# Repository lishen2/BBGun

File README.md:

BBGun
=============
BBGUN is an infrared shooting system used for entertainment purposes. The project Milestag gave us a lot of inspiration.

Hareware resources
-------
* one TSAL6100 IR emitter, two HS0038B IR reciver.
* one RJ9 socket used to connect external reciver(not implemented yet).
* one three key dil switch, used to set group.
* one buzzer controlled by PWM pin.
* two push buttons.

Progress
--------
20150427: First PCB design.     
20150503: Make first test board.  
20150505: LED driver code and buzzer driver code finish.  
20150510: Finish all drivers except IR system.

Developing blog
--------
http://lsgeek.blogspot.com

BBGun
=============
BBGun是一个用于娱乐目的的红外射击系统(真人CS)。Milestag项目给了我们很多启发。

硬件资源
-------
* 一个TSAL6100发射管，两个HS0038B接收管
* 一个RJ9接口用于连接外置接收器（暂未实现）
* 一个三键拨码开关，用于设置分组
* 一个PWM引脚控制的蜂鸣器
* 两个按键

当前进度
--------
20150427: 完成PCB设计   
20150503: 完成第一块PCB的制作   
20150505: 完成LED驱动、蜂鸣器驱动  
20150510: 完成除IR系统外的所有驱动

开发博客
--------
http://blog.sina.com.cn/lgeek

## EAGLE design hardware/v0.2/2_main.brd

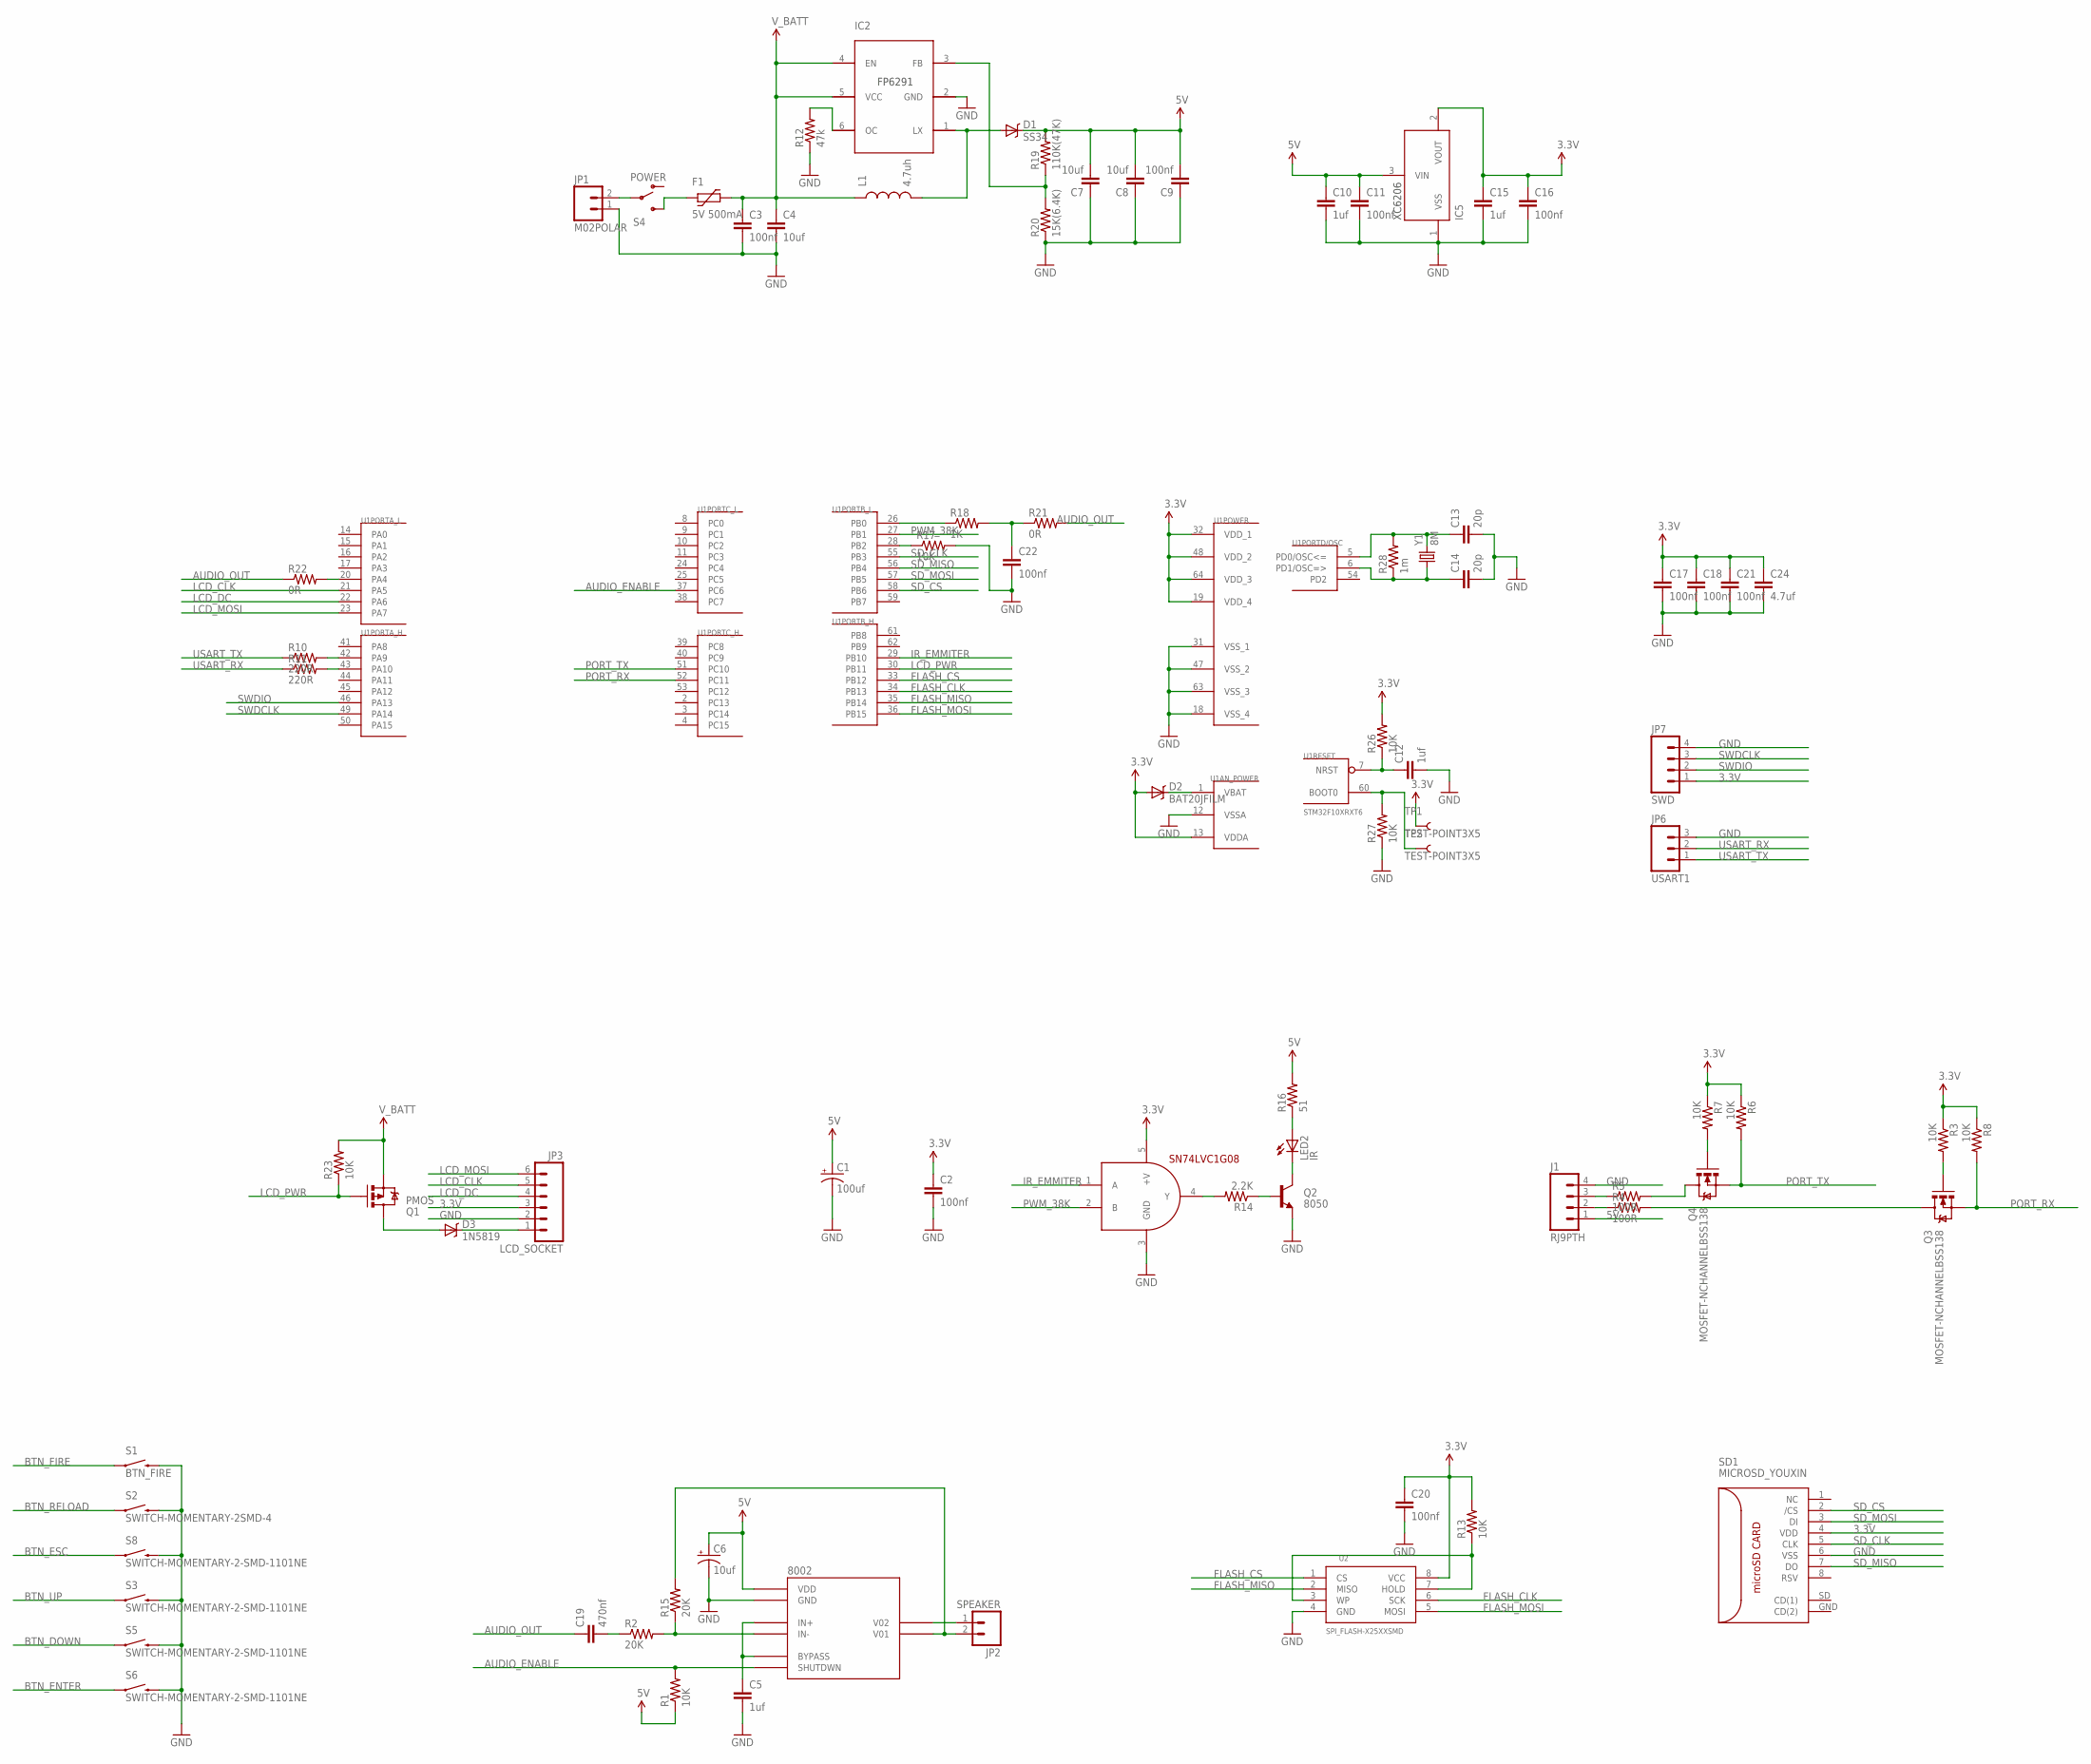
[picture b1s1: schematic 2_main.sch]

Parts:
8002: LM4871; SO08
C1: 100uf; EIA6032
C2, C3, C9, C11, C16, C17, C18, C20, C21, C22: 100nf; 0603-CAP
C4, C7, C8: 10uf; 0603-CAP
C5, C10, C12, C15: 1uf; 0603-CAP
C6: 10uf; EIA3216-KIT
C13, C14: 20p; 0603-CAP
C19: 470nf; 0603-CAP
C24: 4.7uf; 0603-CAP
D1: SS34; SMA-DIODE
D2: BAT20JFILM; SOD-323
D3: 1N5819; SOD-323
F1: 5V 500mA; R0805
IC1: SN74LVC1G08; SOT23-5
IC2: FP6291; SOT23-6
IC5: XC6206; SOT23-3
J1: RJ9PTH; RJ9
JP1: M02POLAR; MOLEX-1X2
JP2: SPEAKER; MOLEX-1X2
JP3: LCD_SOCKET; MOLEX-1X6
JP6: USART1; 1X03
JP7: SWD; 1X04
L1: 4.7uh; CR75_V2
LED2: IR; LED5MM
Q1: PMOS; SOT23-3
Q2: 8050; SOT23
Q3, Q4: MOSFET-NCHANNELBSS138; SOT23
R1, R3, R6, R7, R8, R13, R17, R23, R26, R27: 10K; 0603-RES
R2, R15: 20K; 0603-RES
R4, R5: 100R; 0603-RES
R10, R11: 220R; 0603-RES
R12: 47k; 0603-RES
R14: 2.2K; 0603-RES
R16: 51; 0603-RES
R18: 1K; 0603-RES
R19: 110K(47K); 0603-RES
R20: 15K(6.4K); 0603-RES
R21, R22: 0R; 0603-RES
R28: 1m; 0603-RES
S1: BTN_FIRE; TACTILE_SWITCH_TALL
S2: SWITCH-MOMENTARY-2SMD-4; TACTILE_SWITCH_TALL
S3, S5, S6, S8: SWITCH-MOMENTARY-2-SMD-1101NE; TACTILE-SWITCH-1101NE
S4: POWER; SWITCH-SPDT-AM#6
SD1: MICROSD_YOUXIN; MICRO_SD_YOUXIN
TP1, TP2: TEST-POINT3X5; PAD.03X.05
U1: STM32F10XRXT6; TQFP64
U2: SPI_FLASH-X25XXSMD; SO08
Y1: 8M; CRYSTAL-TXC-7A

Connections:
3.3V: C2.1, C15.1, C16.1, C17.1, C18.1, C20.1, C21.1, C24.1, D2.2 (A), IC1.5 (+V), IC5.2 (VOUT), JP3.3, JP7.1, R3.1, R6.1, R7.1, R8.1, R13.2, R26.2, SD1.4 (VDD), TP1.P$1, U1.13 (VDDA), U1.19 (VDD_4), U1.32 (VDD_1), U1.48 (VDD_2), U1.64 (VDD_3), U2.8 (VCC)
5V: 8002.6 (VDD), C1.P$1 (+), C6.A (+), C7.2, C8.2, C9.2, C10.1, C11.1, D1.C, IC5.3 (VIN), J1.1, R1.1, R16.2, R19.2
AUDIO_ENABLE: 8002.1 (SHUTDWN), R1.2, U1.37 (PC6)
AUDIO_OUT: C19.1, R21.2, R22.1
BTN_DOWN: S5.P$1 (1)
BTN_ENTER: S6.P$1 (1)
BTN_ESC: S8.P$1 (1)
BTN_FIRE: S1.A2 (1)
BTN_RELOAD: S2.A2 (1)
BTN_UP: S3.P$1 (1)
FLASH_CLK: U1.34 (PB13), U2.6 (SCK)
FLASH_CS: U1.33 (PB12), U2.1 (CS)
FLASH_MISO: U1.35 (PB14), U2.2 (MISO)
FLASH_MOSI: U1.36 (PB15), U2.5 (MOSI)
GND: 8002.7 (GND), C1.P$2 (-), C2.2, C3.2, C4.2, C5.2, C6.C (-), C7.1, C8.1, C9.1, C10.2, C11.2, C12.2, C13.2, C14.2, C15.2, C16.2, C17.2, C18.2, C20.2, C21.2, C22.2, C24.2, IC1.3 (GND), IC2.2 (GND), IC5.1 (VSS), J1.4, JP1.1, JP3.2, JP6.3, JP7.4, Q2.2 (E), R12.1, R17.2, R20.1, R27.1, S1.B2 (2), S2.B2 (2), S3.P$2 (2), S5.P$2 (2), S6.P$2 (2), S8.P$2 (2), SD1.6 (VSS), U1.12 (VSSA), U1.18 (VSS_4), U1.31 (VSS_1), U1.47 (VSS_2), U1.63 (VSS_3), U2.4 (GND)
IR_EMMITER: IC1.1 (A), U1.29 (PB10)
LCD_CLK: JP3.5, U1.21 (PA5)
LCD_DC: JP3.4, U1.22 (PA6)
LCD_MOSI: JP3.6, U1.23 (PA7)
LCD_PWR: Q1.1 (G), R23.1, U1.30 (PB11)
unnamed: R17.1, U1.28 (PB2)
unnamed: R27.2, TP2.P$1, U1.60 (BOOT0)
unnamed: C13.1, R28.2, U1.5 (PD0/OSC<=), Y1.P$2 (2)
unnamed: C14.1, R28.1, U1.6 (PD1/OSC=>), Y1.P$1 (1)
unnamed: D2.1 (C), U1.1 (VBAT)
unnamed: IC1.4 (Y), R14.2
unnamed: JP1.2, S4.2
unnamed: LED2.K (C), Q2.3 (C)
unnamed: Q2.1 (B), R14.1
unnamed: F1.1, S4.3 (S)
unnamed: Q3.3 (D), R4.2
unnamed: J1.3, R5.1
unnamed: Q4.3 (D), R5.2
unnamed: R18.1, U1.26 (PB0)
unnamed: 8002.8 (V02), JP2.1
unnamed: Q4.1 (G), R7.2
unnamed: Q3.1 (G), R3.2
unnamed: 8002.5 (V01), JP2.2, R15.2
unnamed: C19.2, R2.1
unnamed: LED2.A, R16.1
unnamed: 8002.4 (IN-), R2.2, R15.1
unnamed: D1.A, IC2.1 (LX), L1.P$2 (2)
unnamed: IC2.6 (OC), R12.2
unnamed: 8002.2 (BYPASS), 8002.3 (IN+), C5.1
unnamed: IC2.3 (FB), R19.1, R20.2
unnamed: R13.1, U2.3 (WP), U2.7 (HOLD)
unnamed: R10.2, U1.42 (PA9)
unnamed: R11.2, U1.43 (PA10)
unnamed: D3.1 (C), JP3.1
unnamed: C22.1, R18.2, R21.1
unnamed: R22.2, U1.20 (PA4)
unnamed: D3.2 (A), Q1.3 (D)
unnamed: J1.2, R4.1
unnamed: C12.1, R26.1, U1.7 (NRST)
PORT_RX: Q3.2 (S), R8.2, U1.52 (PC11)
PORT_TX: Q4.2 (S), R6.2, U1.51 (PC10)
PWM_38K: IC1.2 (B), U1.27 (PB1)
SD_CLK: SD1.5 (CLK), U1.55 (PB3)
SD_CS: SD1.2 (/CS), U1.58 (PB6)
SD_MISO: SD1.7 (DO), U1.56 (PB4)
SD_MOSI: SD1.3 (DI), U1.57 (PB5)
SWDCLK: JP7.3, U1.49 (PA14)
SWDIO: JP7.2, U1.46 (PA13)
USART_RX: JP6.2, R11.1
USART_TX: JP6.1, R10.1
V_BATT: C3.1, C4.1, F1.2, IC2.4 (EN), IC2.5 (VCC), L1.P$1 (1), Q1.2 (S), R23.2

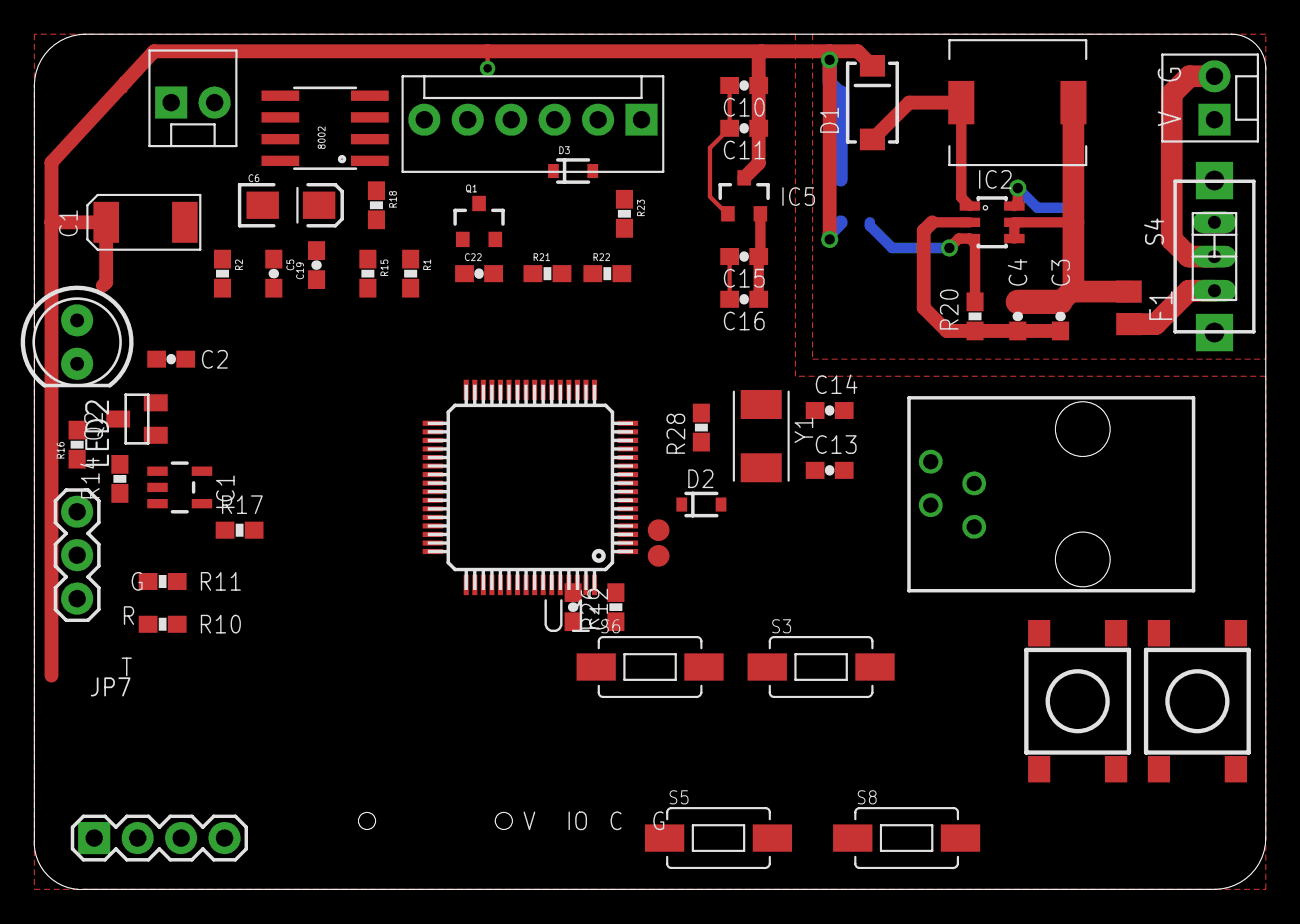
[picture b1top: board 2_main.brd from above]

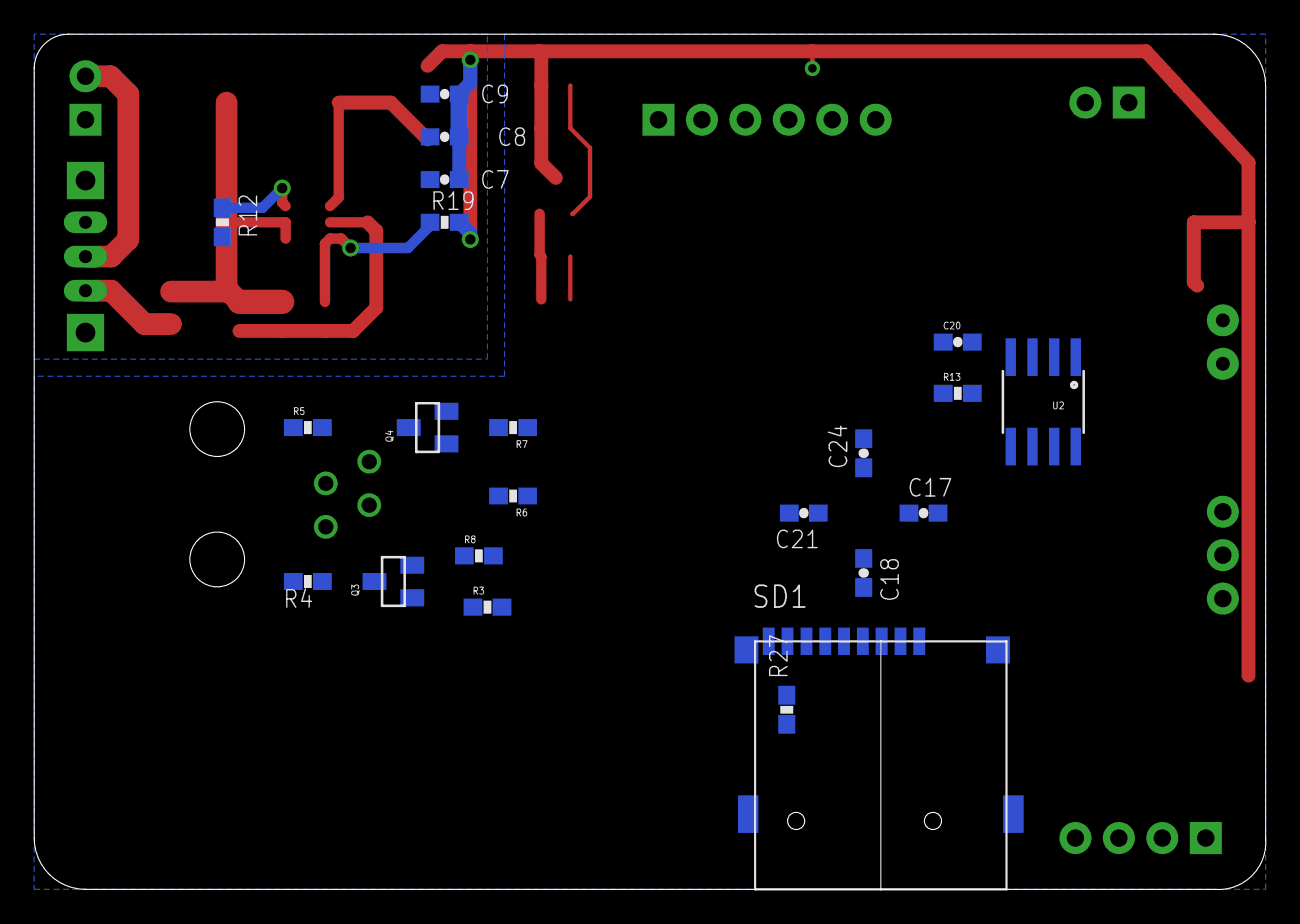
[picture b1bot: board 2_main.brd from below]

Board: 2 copper layers, 72.0 x 50.0 mm, 81 parts (22 on the bottom side), 60 nets.

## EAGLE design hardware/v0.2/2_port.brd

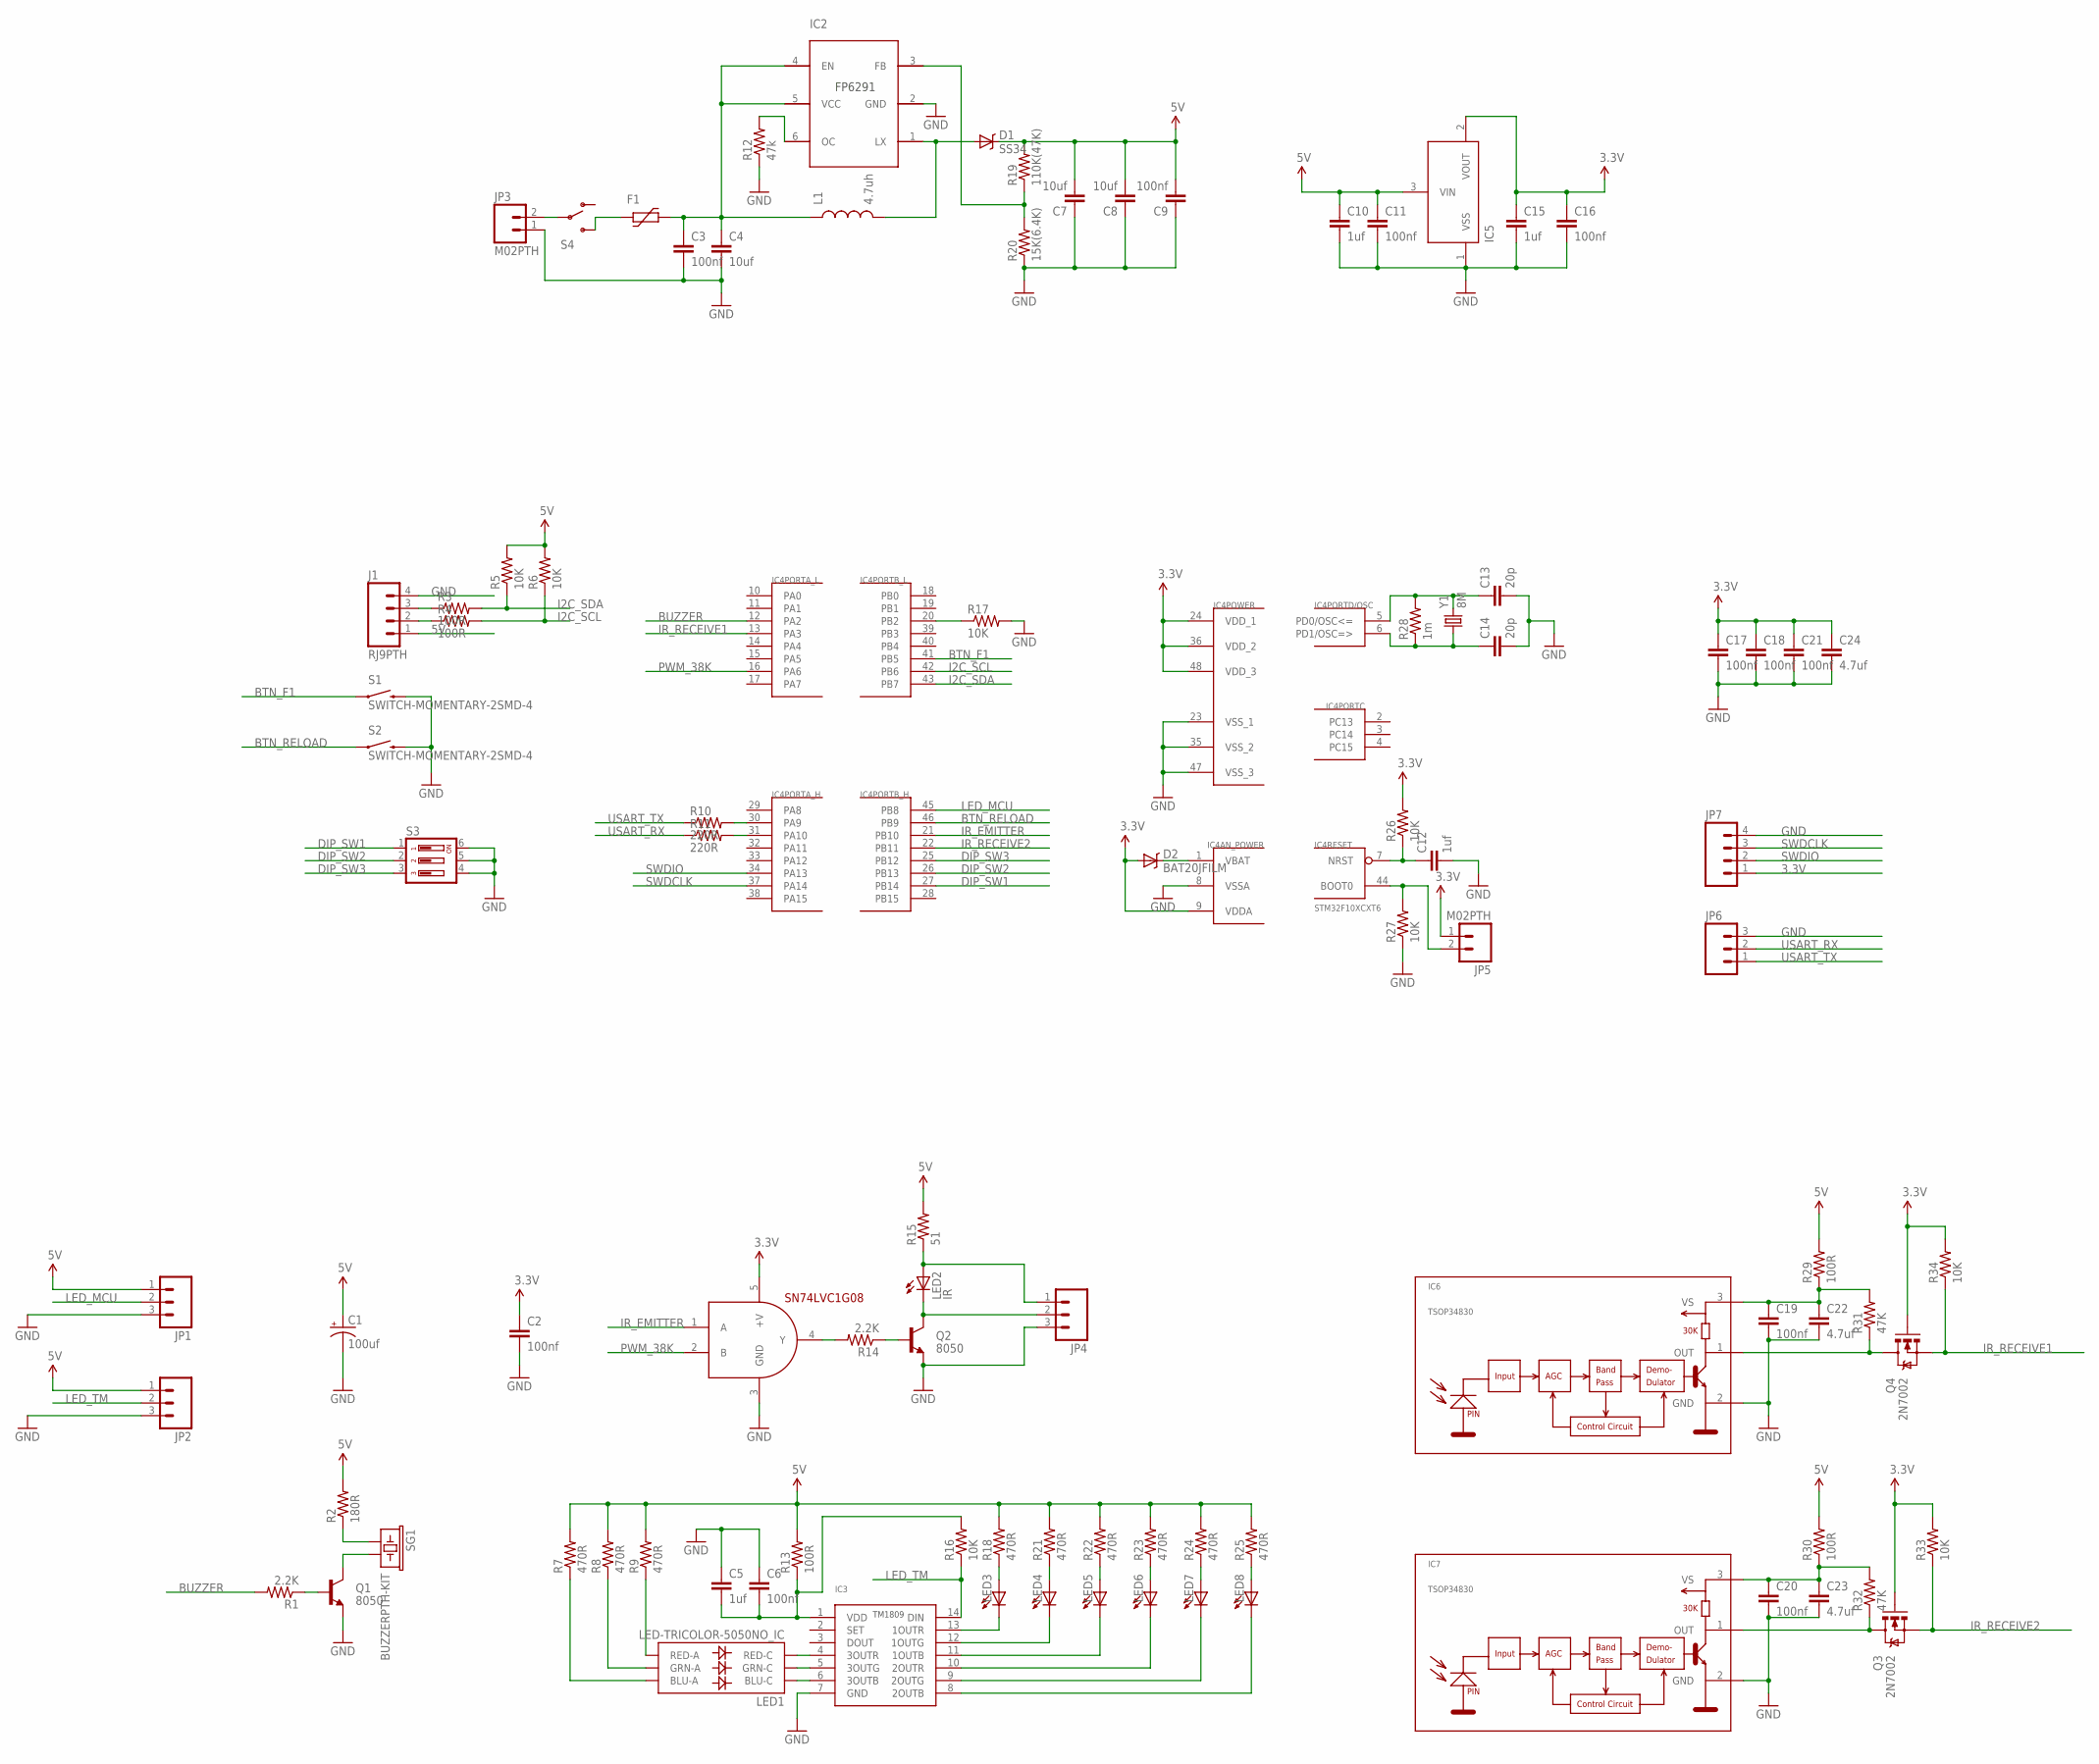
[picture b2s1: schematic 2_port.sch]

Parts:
C1: 100uf; EIA6032
C2, C3, C6, C9, C11, C16, C17, C18, C19, C20, C21: 100nf; 0603-CAP
C4, C7, C8: 10uf; 0603-CAP
C5, C10, C12, C15: 1uf; 0603-CAP
C13, C14: 20p; 0603-CAP
C22, C23, C24: 4.7uf; 0603-CAP
D1: SS34; SMA-DIODE
D2: BAT20JFILM; SOD-323
F1: PTC-FUSE; R0805
IC1: SN74LVC1G08; SOT23-5
IC2: FP6291; SOT23-6
IC3: TM1809; SOP-14
IC4: STM32F10XCXT6; TQFP48
IC5: XC6206; SOT23-3
IC6, IC7: TSOP34830; TSOP348
J1: RJ9PTH; RJ9
JP1, JP2, JP4, JP6: M03PTH; 1X03
JP3, JP5: M02PTH; 1X02
JP7: M04PTH; 1X04
L1: 4.7uh; CR75_V2
LED1: LED-TRICOLOR-5050NO_IC; LED-TRICOLOR-5050
LED2: IR; LED5MM
LED3, LED4, LED5, LED6, LED7, LED8: LED0805; CHIPLED_0805
Q1, Q2: 8050; SOT23
Q3, Q4: 2N7002; SOT23
R1, R14: 2.2K; 0603-RES
R2: 180R; 0603-RES
R3, R4, R13, R29, R30: 100R; 0603-RES
R5, R6, R16, R17, R26, R27, R33, R34: 10K; 0603-RES
R7, R8, R9, R18, R21, R22, R23, R24, R25: 470R; 0603-RES
R10, R11: 220R; 0603-RES
R12: 47k; 0603-RES
R15: 51; 1206
R19: 110K(47K); 0603-RES
R20: 15K(6.4K); 0603-RES
R28: 1m; 0603-RES
R31, R32: 47K; 0603-RES
S1, S2: SWITCH-MOMENTARY-2SMD-4; TACTILE_SWITCH_TALL
S3: DIP03YL
S4: SWITCH-SPST3AM6; SWITCH-SPDT-AM#6
SG1: BUZZERPTH-KIT; BUZZER-12MM-KIT
Y1: 8M; CRYSTAL-TXC-7A

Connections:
3.3V: C2.1, C15.1, C16.1, C17.1, C18.1, C21.1, C24.1, D2.2 (A), IC1.5 (+V), IC4.9 (VDDA), IC4.24 (VDD_1), IC4.36 (VDD_2), IC4.48 (VDD_3), IC5.2 (VOUT), JP5.1, JP7.1, Q3.1 (G), Q4.1 (G), R26.2, R33.2, R34.2
5V: C1.P$1 (+), C7.2, C8.2, C9.2, C10.1, C11.1, D1.C, IC5.3 (VIN), J1.1, JP1.1, JP2.1, R2.2, R5.2, R6.2, R7.2, R8.2, R9.2, R13.2, R15.2, R18.2, R19.2, R21.2, R22.2, R23.2, R24.2, R25.2, R29.2, R30.2
BTN_F1: IC4.41 (PB5), S1.A2 (1)
BTN_RELOAD: IC4.46 (PB9), S2.A2 (1)
BUZZER: IC4.12 (PA2), R1.2
DIP_SW1: IC4.27 (PB14), S3.1
DIP_SW2: IC4.26 (PB13), S3.2
DIP_SW3: IC4.25 (PB12), S3.3
GND: C1.P$2 (-), C2.2, C3.2, C4.2, C5.1, C6.1, C7.1, C8.1, C9.1, C10.2, C11.2, C12.2, C13.2, C14.2, C15.2, C16.2, C17.2, C18.2, C19.2, C20.2, C21.2, C22.2, C23.2, C24.2, IC1.3 (GND), IC2.2 (GND), IC3.7 (GND), IC4.8 (VSSA), IC4.23 (VSS_1), IC4.35 (VSS_2), IC4.47 (VSS_3), IC5.1 (VSS), IC6.2 (GND), IC7.2 (GND), J1.4, JP1.3, JP2.3, JP3.1, JP4.3, JP6.3, JP7.4, Q1.2 (E), Q2.2 (E), R12.1, R17.2, R20.1, R27.1, S1.B2 (2), S2.B2 (2), S3.4, S3.5, S3.6
I2C_SCL: IC4.42 (PB6), R4.2, R6.1
I2C_SDA: IC4.43 (PB7), R3.2, R5.1
IR_EMITTER: IC1.1 (A), IC4.21 (PB10)
IR_RECEIVE1: IC4.13 (PA3), Q4.2 (S), R34.1
IR_RECEIVE2: IC4.22 (PB11), Q3.2 (S), R33.1
LED_MCU: IC4.45 (PB8), JP1.2
LED_TM: IC3.14 (DIN), JP2.2, R16.1
unnamed: IC4.20 (PB2), R17.1
unnamed: IC4.44 (BOOT0), JP5.2, R27.2
unnamed: C13.1, IC4.5 (PD0/OSC<=), R28.2, Y1.P$2 (2)
unnamed: C14.1, IC4.6 (PD1/OSC=>), R28.1, Y1.P$1 (1)
unnamed: D2.1 (C), IC4.1 (VBAT)
unnamed: IC1.4 (Y), R14.2
unnamed: JP3.2, S4.2
unnamed: JP4.2, LED2.K (C), Q2.3 (C)
unnamed: Q2.1 (B), R14.1
unnamed: F1.1, S4.3 (S)
unnamed: C19.1, C22.1, IC6.3 (VS), R29.1, R31.2
unnamed: C20.1, C23.1, IC7.3 (VS), R30.1, R32.2
unnamed: IC3.4 (3OUTR), LED1.5 (RED-C)
unnamed: JP4.1, LED2.A, R15.1
unnamed: IC3.5 (3OUTG), LED1.6 (GRN-C)
unnamed: IC3.6 (3OUTB), LED1.4 (BLU-C)
unnamed: LED1.2 (RED-A), R9.1
unnamed: LED1.1 (GRN-A), R8.1
unnamed: LED1.3 (BLU-A), R7.1
unnamed: C3.1, C4.1, F1.2, IC2.4 (EN), IC2.5 (VCC), L1.P$1 (1)
unnamed: IC3.13 (1OUTR), LED3.C
unnamed: D1.A, IC2.1 (LX), L1.P$2 (2)
unnamed: IC2.6 (OC), R12.2
unnamed: LED3.A, R18.1
unnamed: IC2.3 (FB), R19.1, R20.2
unnamed: LED4.A, R21.1
unnamed: IC3.12 (1OUTG), LED4.C
unnamed: IC3.11 (1OUTB), LED5.C
unnamed: IC3.10 (2OUTR), LED6.C
unnamed: IC3.9 (2OUTG), LED7.C
unnamed: IC3.8 (2OUTB), LED8.C
unnamed: LED5.A, R22.1
unnamed: LED6.A, R23.1
unnamed: LED7.A, R24.1
unnamed: LED8.A, R25.1
unnamed: C5.2, C6.2, IC3.1 (VDD), R13.1, R16.2
unnamed: IC4.30 (PA9), R10.2
unnamed: IC4.31 (PA10), R11.2
unnamed: J1.3, R3.1
unnamed: J1.2, R4.1
unnamed: R2.1, SG1.+ (1)
unnamed: Q1.3 (C), SG1.- (2)
unnamed: Q1.1 (B), R1.1
unnamed: C12.1, IC4.7 (NRST), R26.1
unnamed: IC6.1 (OUT), Q4.3 (D), R31.1
unnamed: IC7.1 (OUT), Q3.3 (D), R32.1
PWM_38K: IC1.2 (B), IC4.16 (PA6)
SWDCLK: IC4.37 (PA14), JP7.3
SWDIO: IC4.34 (PA13), JP7.2
USART_RX: JP6.2, R11.1
USART_TX: JP6.1, R10.1

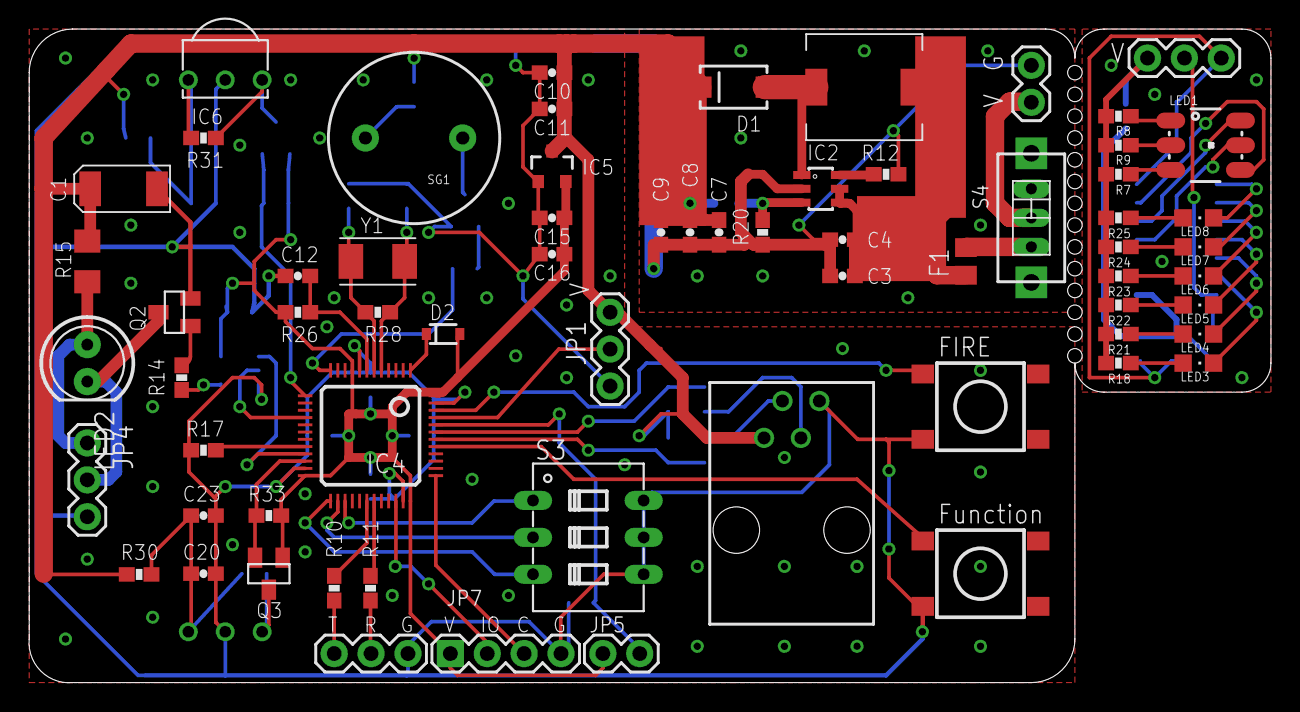
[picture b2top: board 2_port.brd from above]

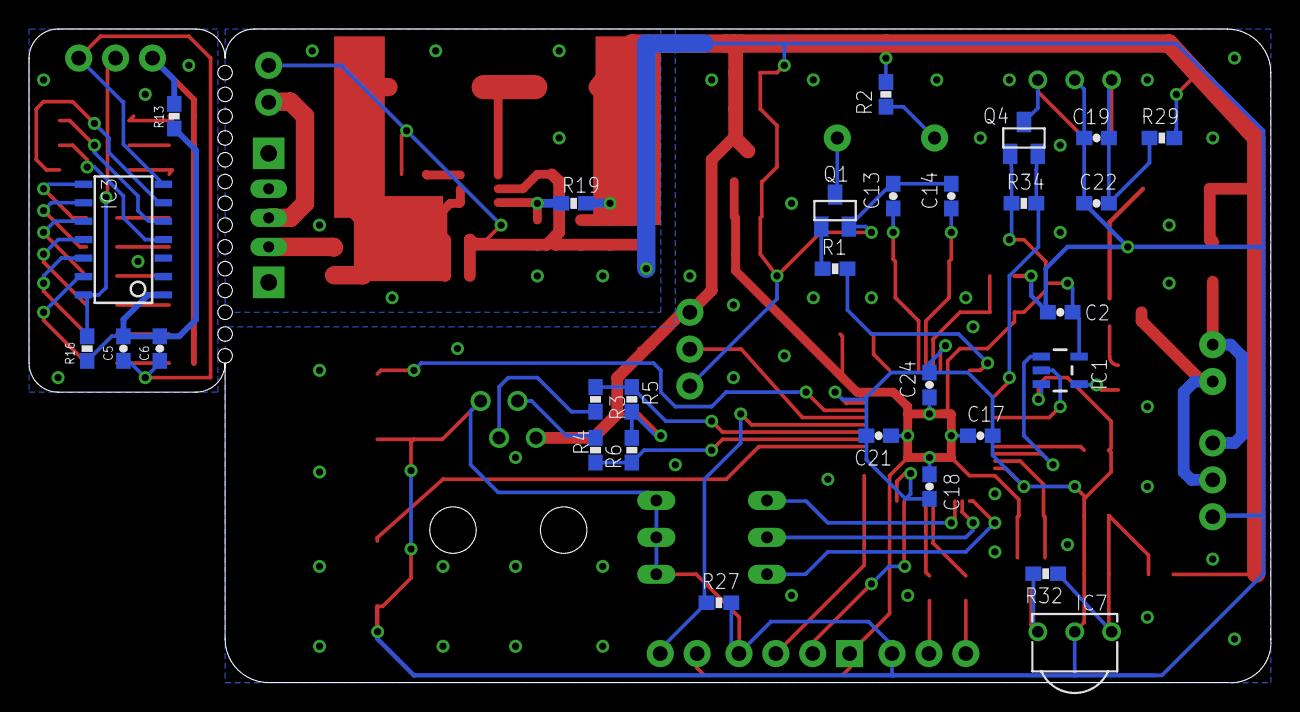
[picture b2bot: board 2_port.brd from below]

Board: 2 copper layers, 85.5 x 45.0 mm, 95 parts (29 on the bottom side), 67 nets.

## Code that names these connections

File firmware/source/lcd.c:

#include "stm32f10x.h"
#include "public.h"
#include "lcd.h"

#define LED_WIDTH_PIXEL  128
#define LED_PAGES        8

#define LCD_MOSI_RCC	  RCC_APB2Periph_GPIOA
#define LCD_MOSI_PORT	  GPIOA
#define LCD_MOSI_PIN	  GPIO_Pin_7

#define LCD_CLK_RCC		  RCC_APB2Periph_GPIOA
#define LCD_CLK_PORT	  GPIOA
#define LCD_CLK_PIN		  GPIO_Pin_5

#define LCD_RST_RCC		  RCC_APB2Periph_GPIOA
#define LCD_RST_PORT	  GPIOA
#define LCD_RST_PIN		  GPIO_Pin_3

#define LCD_DC_RCC		  RCC_APB2Periph_GPIOA
#define LCD_DC_PORT		  GPIOA
#define LCD_DC_PIN 		  GPIO_Pin_4

#define LCD_SPI           SPI1
#define LCD_SPI_RCC       RCC_APB2Periph_SPI1
#define LCD_DMA_CHANNEL   DMA1_Channel3
#define LCD_DMA_TC_FLAG   DMA1_FLAG_TC3

static uint8_t g_framebuffer[LED_PAGES][LED_WIDTH_PIXEL];

static void _gpioInit(void)
{
	GPIO_InitTypeDef GPIO_InitStructure;

	RCC_APB2PeriphClockCmd(LCD_MOSI_RCC|LCD_CLK_RCC|LCD_RST_RCC|LCD_DC_RCC, ENABLE);

	GPIO_InitStructure.GPIO_Pin = LCD_MOSI_PIN;
	GPIO_InitStructure.GPIO_Speed = GPIO_Speed_50MHz;
	GPIO_InitStructure.GPIO_Mode = GPIO_Mode_AF_PP;
	GPIO_Init(LCD_MOSI_PORT, &GPIO_InitStructure);	

	GPIO_InitStructure.GPIO_Pin = LCD_CLK_PIN;
	GPIO_InitStructure.GPIO_Speed = GPIO_Speed_50MHz;
	GPIO_InitStructure.GPIO_Mode = GPIO_Mode_AF_PP;
	GPIO_Init(LCD_CLK_PORT, &GPIO_InitStructure);	

	GPIO_InitStructure.GPIO_Pin = LCD_RST_PIN;
	GPIO_InitStructure.GPIO_Speed = GPIO_Speed_50MHz;
	GPIO_InitStructure.GPIO_Mode = GPIO_Mode_Out_PP;
	GPIO_Init(LCD_RST_PORT, &GPIO_InitStructure);
	GPIO_SetBits(LCD_RST_PORT, LCD_RST_PIN);	

	GPIO_InitStructure.GPIO_Pin = LCD_DC_PIN;
	GPIO_InitStructure.GPIO_Speed = GPIO_Speed_50MHz;
	GPIO_InitStructure.GPIO_Mode = GPIO_Mode_Out_PP;
	GPIO_Init(LCD_DC_PORT, &GPIO_InitStructure);	

	return;
}

static void _spiInit(void)
{
	SPI_InitTypeDef  SPI_InitStructure;

	RCC_APB2PeriphClockCmd(LCD_SPI_RCC, ENABLE);

	/* SPI1 configuration */ 
	SPI_InitStructure.SPI_Direction = SPI_Direction_1Line_Tx; 
	SPI_InitStructure.SPI_Mode = SPI_Mode_Master;	                   
	SPI_InitStructure.SPI_DataSize = SPI_DataSize_8b;                  
	SPI_InitStructure.SPI_CPOL = SPI_CPOL_High;	 		               
	SPI_InitStructure.SPI_CPHA = SPI_CPHA_2Edge;		               
	SPI_InitStructure.SPI_NSS = SPI_NSS_Soft;			               
	SPI_InitStructure.SPI_BaudRatePrescaler = SPI_BaudRatePrescaler_2; 
	SPI_InitStructure.SPI_FirstBit = SPI_FirstBit_MSB;				   
	SPI_InitStructure.SPI_CRCPolynomial = 7;						   
	SPI_Init(LCD_SPI, &SPI_InitStructure);
    SPI_I2S_DMACmd(LCD_SPI, SPI_I2S_DMAReq_Tx, ENABLE);
	SPI_Cmd(LCD_SPI, ENABLE);

	return;
}

static void _spi_writeByte(u8 txData)
{						 		  
	LCD_SPI->DR = txData;
	while (SPI_I2S_GetFlagStatus(SPI_FLASH_SPI, SPI_I2S_FLAG_RXNE) == RESET) { ; }

    return;
}

static void _lcdWriteCmd(unsigned char cmd)
{
	GPIO_ResetBits(LCD_DC_PORT, LCD_DC_PIN);
	_spi_writeByte(cmd);
	return;
}

static void _lcdSetup(void)
{	 
	/* reset led */
	GPIO_ResetBits(LCD_RST_PORT, LCD_RST_PIN);
	delay_ms(50);
	GPIO_SetBits(LCD_RST_PORT, LCD_RST_PIN);

	/* ¹Ø±ÕÏÔÊ¾ */
	_lcdWriteCmd(0xae);// Turn off oled panel
	_lcdWriteCmd(0x40);// Set Display Start Line (40h~7Fh)
	
	/* ÉèÖÃÁÁ¶È */
	_lcdWriteCmd(0x81);//--set contrast control register
	_lcdWriteCmd(0xcf);// Set SEG Output Current Brightness

	_lcdWriteCmd(0xa1);//--Set SEG/Column Mapping     0xa0×óÓÒ·´ÖÃ 0xa1Õý³£
	_lcdWriteCmd(0xc8);//Set COM/Row Scan Direction   0xc0ÉÏÏÂ·´ÖÃ 0xc8Õý³£
	_lcdWriteCmd(0xa6);//--set normal display

	_lcdWriteCmd(0xa8);//--set multiplex ratio(1 to 64)
	_lcdWriteCmd(0x3f);

	_lcdWriteCmd(0xd3);//-set display offset	Shift Mapping RAM Counter (0x00~0x3F)
	_lcdWriteCmd(0x00);//-not offset

	_lcdWriteCmd(0xd5);//--set display clock divide ratio/oscillator frequency
	_lcdWriteCmd(0x80);//--set divide ratio, Set Clock as 100 Frames/Sec

	_lcdWriteCmd(0xd9);//--set pre-charge period
	_lcdWriteCmd(0xf1);//Set Pre-Charge as 15 Clocks & Discharge as 1 Clock

	_lcdWriteCmd(0xda);//--set com pins hardware configuration
	_lcdWriteCmd(0x12);

	_lcdWriteCmd(0xdb);//--set vcomh
	_lcdWriteCmd(0x40);//Set VCOM Deselect Level

	_lcdWriteCmd(0x20);//-Set Page Addressing Mode (0x00/0x01/0x02)
	_lcdWriteCmd(0x00);//Ê¹ÓÃË®Æ½Ä£Ê½

	//ÉèÖÃÐÐÉ¨Ãè·¶Î§ºÍpageÉ¨Ãè·¶Î§
	_lcdWriteCmd(0x21);//-Set Column Address Range
	_lcdWriteCmd(0x00);
	_lcdWriteCmd(0x7F);

	_lcdWriteCmd(0x22);
	_lcdWriteCmd(0x00);//-Set Page Address Rage
	_lcdWriteCmd(0x07);

	_lcdWriteCmd(0x8d);//--set Charge Pump enable/disable
	_lcdWriteCmd(0x14);//--set(0x10) disable
	_lcdWriteCmd(0xa4);// Disable Entire Display On (0xa4/0xa5)
	_lcdWriteCmd(0xa6);// Disable Inverse Display On (0xa6/a7) 
	_lcdWriteCmd(0xaf);//--turn on oled panel

	return;
}

static void _flushhBuffer(void)
{
    DMA_InitTypeDef DMA_InitStructure;  

    //wait last transfer finish
    while(!DMA_GetFlagStatus(LCD_DMA_TC_FLAG));
    DMA_Cmd(LCD_DMA_CHANNEL, DISABLE);  //TODO, verify if this is necessary
    
    DMA_InitStructure.DMA_PeripheralBaseAddr = (uint32_t)(LCD_SPI->DR);
    DMA_InitStructure.DMA_MemoryBaseAddr = (uint32_t)g_framebuffer;
    DMA_InitStructure.DMA_DIR = DMA_DIR_PeripheralDST;
    DMA_InitStructure.DMA_BufferSize = sizeof(g_framebuffer);
    DMA_InitStructure.DMA_PeripheralInc = DMA_PeripheralInc_Disable;
    DMA_InitStructure.DMA_MemoryInc = DMA_MemoryInc_Enable;
    DMA_InitStructure.DMA_PeripheralDataSize = DMA_PeripheralDataSize_Byte;
    DMA_InitStructure.DMA_MemoryDataSize = DMA_MemoryDataSize_Byte;
    DMA_InitStructure.DMA_Mode = DMA_Mode_Normal;
    DMA_InitStructure.DMA_Priority = DMA_Priority_High;
    DMA_InitStructure.DMA_M2M = DMA_M2M_Disable;
    DMA_Init(LCD_DMA_CHANNEL, &DMA_InitStructure);

    DMA_Cmd(LCD_DMA_CHANNEL, ENABLE);
    return;
}

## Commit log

2015-04-19 modify readme
2015-04-19 add schematic
2015-04-19 start wiring
2015-04-20 wiring
2015-04-23 nearly finish
2015-04-24 finish wire
2015-04-25 finish
2015-04-26 found some mistake, wait fixup
2015-04-27 modify some packages
2015-05-04 update silkscreen
2015-05-05 update README.md , add two pictures
2015-05-05 fixing misspell
2015-05-10 add firmware version 0.1, all peripheral done except IR system
2015-05-10 update progress
2015-05-11 add link to blog
2015-05-18 fix switch issue
2015-08-29 writing...
2015-09-01 writing code
2015-09-01 repair compile issue
2015-09-02 writing
2015-09-05 drawing v0.2 pcb
2015-09-06 update sch
2015-09-08 continue writing code
2015-09-09 add mirco sd socket
2015-09-10 update pcb

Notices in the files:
parts and their libraries:
SparkFun-Passives: Licensing: CC v3.0 Share-Alike You are welcome to use this library for commercial purposes.
